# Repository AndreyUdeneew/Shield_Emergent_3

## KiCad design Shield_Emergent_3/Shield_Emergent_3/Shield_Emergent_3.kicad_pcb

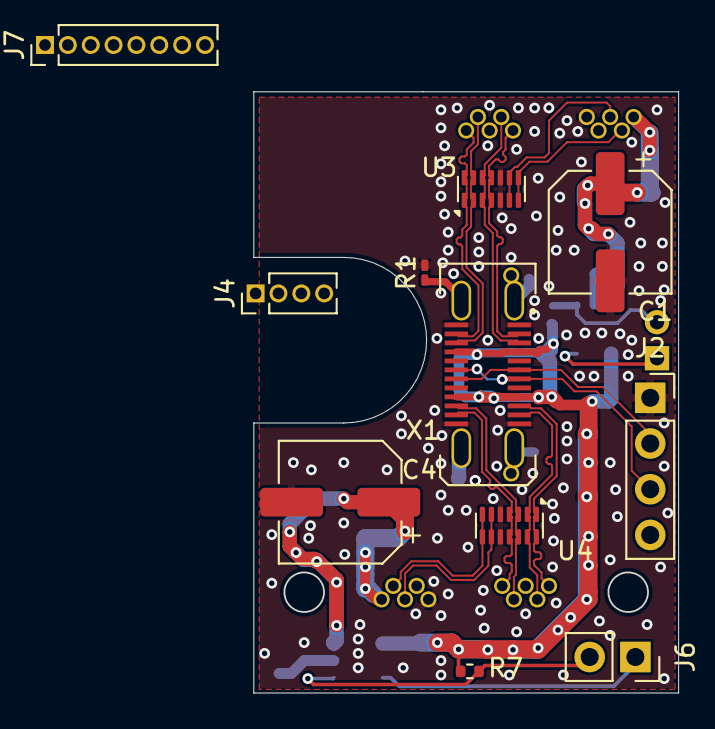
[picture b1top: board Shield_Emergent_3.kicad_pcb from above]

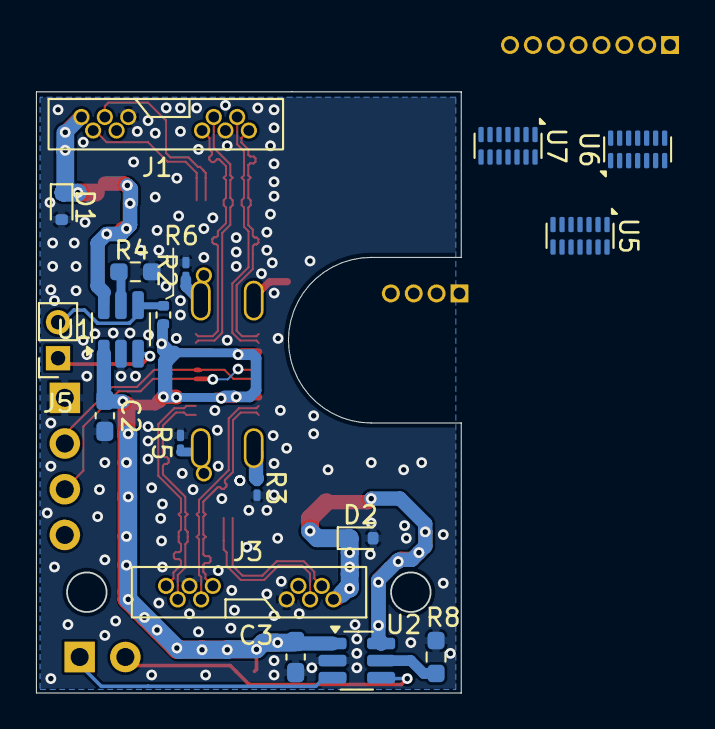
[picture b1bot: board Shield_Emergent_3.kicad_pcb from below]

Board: 4 copper layers, 23.6 x 33.4 mm, 29 parts (18 on the bottom side), 36 nets.

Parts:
C1, C4: 120 uF; CP_Elec_6.3x7.7
C2, C3: 0.1; C_0603_1608Metric_Pad1.08x0.95mm_HandSolder
D1, D2: D_TVS; D_SOD-523
J1, J3: USB3_B_Micro; MU3MS04
J2: Conn_01x04_Socket; PinSocket_1x04_P2.54mm_Vertical
J4: Conn_01x07; PinHeader_1x04_P1.27mm_Vertical
J5: Conn_01x02_Socket; PinSocket_1x02_P2.00mm_Vertical
J6: Conn_01x02_Socket; PinSocket_1x02_P2.54mm_Vertical
J7: Conn_01x08; PinHeader_1x08_P1.27mm_Vertical
R1, R2, R3, R5: 0; R_0201_0603Metric_Pad0.64x0.40mm_HandSolder
R4, R8: R; R_0603_1608Metric_Pad0.98x0.95mm_HandSolder
R6, R7: 100k; R_0402_1005Metric
U1, U2: SOT-23-6_Handsoldering
U3, U4, U5, U6, U7: SP3012-06UTG; DFN-14_1.35x3.5mm_P0.5mm
X1: USB_C_24pins; USB_C_Receptacle_JAE_DX07S024WJ3R400

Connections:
2_D+: J3.3 (D+), U4.6, U4.9
2_D-: J3.2 (D-), U4.7, U4.8
D+: J1.3 (D+), J2.2, U3.6, U3.9, X1.A6 (D+), X1.B6 (D+)
D-: J1.2 (D-), J2.3, U3.7, U3.8, X1.A7 (D-), X1.B7 (D-)
EN1: J5.1, U1.3 (EN)
EN2: J6.1, U2.3 (EN)
GND: C1.2, C2.2, C3.2, C4.2, D1.2 (A2), D2.2 (A2), J1.5 (GND), J1.8 (DRAIN), J2.1, J3.5 (GND), J3.8 (DRAIN), J7.8, R1.2, R2.2, R3.2, R4.2, R5.2, R8.2, U1.2 (GND), U2.2 (GND), U3.5, U3.10, U4.5, U4.10, U5.5, U5.10, U6.5, U6.10, U7.5, U7.10, X1.A1 (GND), X1.A12 (GND), X1.B1 (GND), X1.B12 (GND)
K1: J4.1, U5.1, U5.14
K2: J4.2, U5.2, U5.13
K3: J4.3, U5.3, U5.12
K4: J4.4, U5.4, U5.11
K5: U5.6, U5.9
K6: U5.7, U5.8
K7: U6.3, U6.12
K8: J7.1, U6.2, U6.13
K9: J7.2, U6.1, U6.14
K10: J7.3, U6.6, U6.9
K11: J7.4, U6.7, U6.8
K12: J7.5, U7.6, U7.9
K13: J7.6, U7.7, U7.8
unnamed: R4.1, U1.5 (ILIM)
unnamed: R8.1, U2.5 (ILIM)
RX1+: J1.10 (SSRX+), U3.1, U3.14, X1.B11 (RX1+)
RX1-: J1.9 (SSRX-), U3.2, U3.13, X1.B10 (RX1-)
RX2+: J3.10 (SSRX+), U4.1, U4.14, X1.A10 (RX2-)
RX2-: J3.9 (SSRX-), U4.2, U4.13, X1.A11 (RX2+)
Shield: R1.1, R2.1, R3.1, R5.1, X1.S1 (SHIELD)
TX1+: J1.7 (SSTX+), U3.3, U3.12, X1.A3 (TX1-)
TX1-: J1.6 (SSTX-), U3.4, U3.11, X1.A2 (TX1+)
TX2+: J3.6 (SSTX-), U4.4, U4.11, X1.B2 (TX2+)
TX2-: J3.7 (SSTX+), U4.3, U4.12, X1.B3 (TX2-)
VBUS: C2.1, C3.1, J2.4, R6.2, R7.2, U1.1 (IN), U2.1 (IN), X1.A4 (VBUS), X1.A9 (VBUS), X1.B4 (VBUS), X1.B9 (VBUS)
VOUT1: C1.1, D1.1 (A1), J1.1 (VBUS), U1.6 (OUT)
VOUT2: C4.1, D2.1 (A1), J3.1 (VBUS), U2.6 (OUT)
nFLT1: J5.2, R6.1, U1.4 (nFAULT)
nFLT2: J6.2, R7.1, U2.4 (nFAULT)

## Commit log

2024-05-27 v0.1 Circuit draft was created
2024-06-02 v0.2 some additions in the circuit
2024-06-02 v0.3 USB outputs ant TVSs are in circuit
2024-06-02 v0.4 Circuit was modified. Seems 2B completed
2024-06-06 v0.5 Management connector was added
2024-06-08 v0.6 draft circuit, draft decomposition
2024-06-08 v0.7 nets were modified footprints were corrected Rdy 4 decomposition.
2024-06-10 v0.8 Partial decomposition was completed
2024-06-10 v0.9 Decomposition seems 2B completed
2024-06-10 v1.0 Geometry was modified
2024-06-11 v1.1 Geometry was established, LF routing was completed
2024-06-11 v1.2 internal layers were added
2024-06-11 v1.3 draft routing was completed
2024-06-13 v1.4 draft ruting was totally completed.
2024-06-13 v1.5 some DRC errors were corrected
2024-06-19 v1.6 routing is nearly completed
2024-06-21 v1.7 Keyboard connector was added, decomposed and routed
2024-06-22 v1.8 ESD protection 4 buttons was added
2024-07-01 v1.9 Ordered version was added
2024-08-05 v2.0 Draft routing of RP2040 & keyboard cinnectors ESD protec 4 keyboard
2024-08-15 v2.1 prothos 4 15-pin connector
